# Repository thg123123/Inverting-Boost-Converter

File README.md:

# Inverting Boost Converter: Design & Transient Analysis

**Focus:** Power Electronics | PCB Design | Circuit Simulation

This repository documents the end-to-end design of an inverting boost (buck-boost) converter. It includes the theoretical circuit validation using LTspice transient analysis and the physical 2-layer PCB layout translated into KiCad. 

## ⚡ Design & Simulation Highlights
*   **Topology:** Designed an inverting boost converter to provide a negative output voltage from a positive input supply.
*   **Transient Validation:** Simulated switching characteristics, inductor current ripple, and output voltage ripple using LTspice to ensure power delivery meets baseline design constraints before fabrication.
*   **PCB Layout:** Routed the physical board in KiCad, emphasizing optimized trace widths for high-current paths and minimizing the switching node loop area to reduce parasitic inductance and EMI.

## 🗂️ Repository Structure

*   **`/KiCad Design`**: Contains the complete physical board design.
    *   `schematic.kicad_sch`: The physical circuit schematic.
    *   `PCB.kicad_pcb`: The finalized PCB layout.
    *   **/3D Viewer**: Contains visual renders of the populated board.
*   **`/LTspice Simulation`**: Contains the theoretical validation files.
    *   `Schematic.asc`: The LTspice circuit model.
    *   `TransientAnalysis.plt`: Plot settings and results for the converter's transient response and ripple verification.

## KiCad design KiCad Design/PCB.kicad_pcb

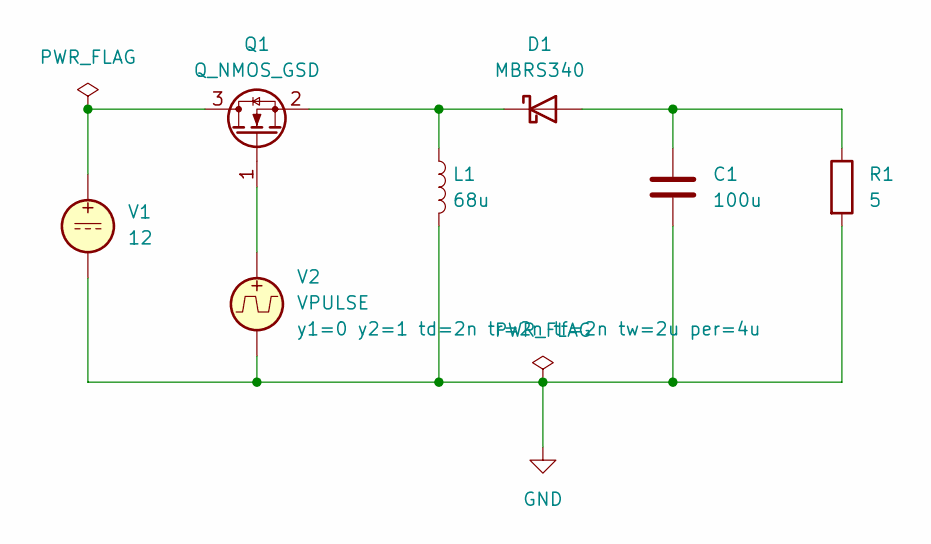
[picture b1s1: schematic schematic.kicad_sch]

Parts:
C1: 100u; CP_Axial_L10.0mm_D4.5mm_P15.00mm_Horizontal
D1: MBRS340; D_SMC
L1: 68u; L_Axial_L5.0mm_D3.6mm_P10.00mm_Horizontal_Murata_BL01RN1A2A2
Q1: Q_NMOS_GSD; TO-220-3_Horizontal_TabDown
R1: 5; R_Axial_DIN0204_L3.6mm_D1.6mm_P1.90mm_Vertical
V1: 12; TerminalBlock_Phoenix_MKDS-1,5-2-5.08_1x02_P5.08mm_Horizont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
V2: VPULSE; TerminalBlock_Phoenix_MKDS-1,5-2-5.08_1x02_P5.08mm_Horizont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

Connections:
GND: C1.2, L1.2, R1.2, V1.2, V2.2
unnamed: C1.1, D1.2 (A), R1.1
unnamed: D1.1 (K), L1.1, Q1.2 (S)
unnamed: Q1.3 (D), V1.1
unnamed: Q1.1 (G), V2.1

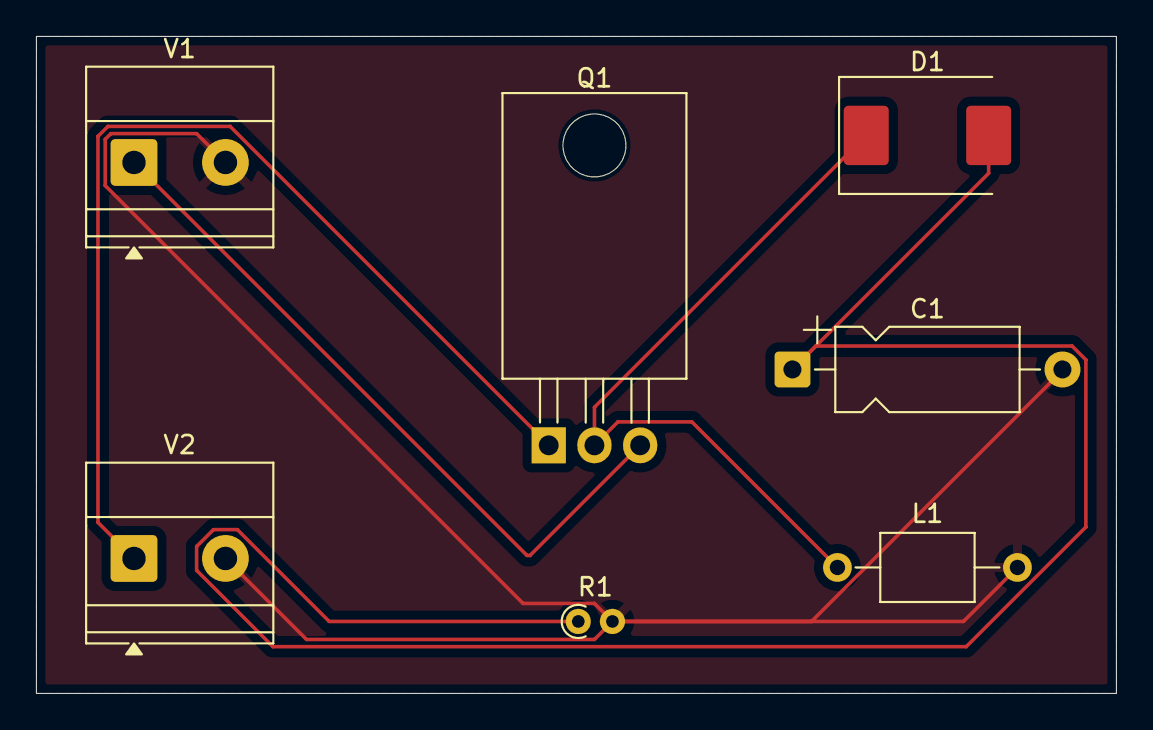
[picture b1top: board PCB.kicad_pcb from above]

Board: 2 copper layers, 60.0 x 36.5 mm, 7 parts (0 on the bottom side), 5 nets.

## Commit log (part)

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2025-12-05 Rename bbc.asc to boostConverterSchematic.asc
2025-12-05 Rename bbc.plt to boostConvertTransientAnalysis.plt
2025-12-05 Rename boostConvertTransientAnalysis.plt to boostConverterTransientAnalysis.plt
2025-12-05 Rename boostConverterSchematic.asc to Schematic.asc
2025-12-05 Rename boostConverterTransientAnalysis.plt to TransientAnalysis.plt
2025-12-05 Rename Boost Converter KiCad Design/buckBoost.1.png to KiCad Design/3D Viewer/Picture 1
2025-12-05 Rename Picture 1 to picture1.png
2025-12-05 Rename Boost Converter KiCad Design/buckBoost.2.png to KiCad Design/3D Viewer/picture2.png
2025-12-05 Rename buckBoost.kicad_prl to preference.kicad_prl
2025-12-05 Rename buckBoost.kicad_pro to project.kicad_pro
2025-12-05 Rename Boost Converter KiCad Design/buckBoost.png to KiCad Design/3D Viewer/picture3.png
2025-12-05 Rename fp-info-cache to Footprint Info
